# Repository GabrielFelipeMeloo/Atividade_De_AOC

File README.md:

# Atividade_De_AOC
Repositório para a entrega da atividade de ponto extra da disciplina de AOC, referente ao dia 28/10/25

### Valor: 150
150=50(mão de obra)+ 100 de custo de materiais

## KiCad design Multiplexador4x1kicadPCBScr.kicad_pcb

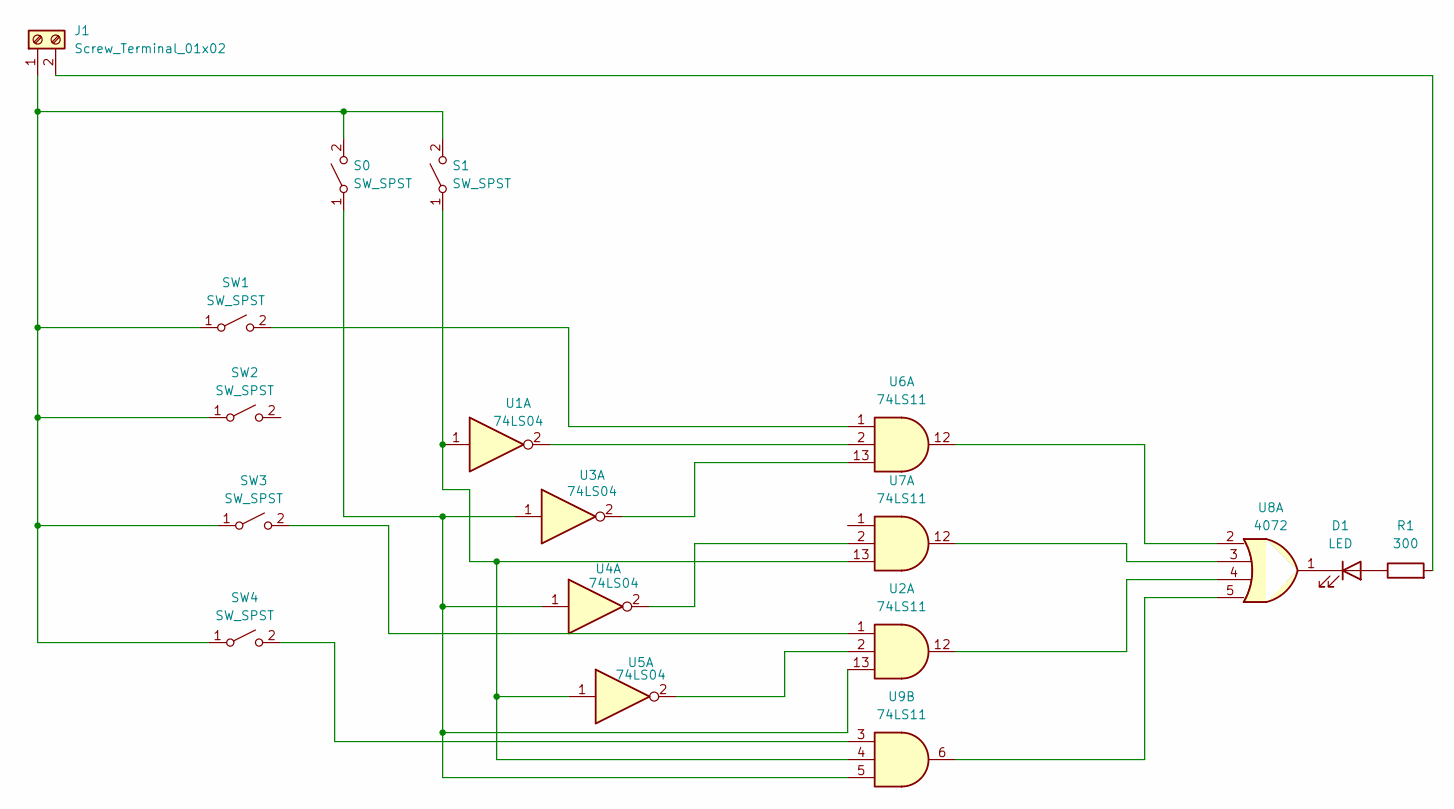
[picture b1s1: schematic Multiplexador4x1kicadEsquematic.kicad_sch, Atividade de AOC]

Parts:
D1: LED; LED_D5.0mm
J1: Screw_Terminal_01x02; PhoenixContact_MSTB_2,5_2-GF_1x02_P5.00mm_Horizontal_Thread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
R1: 300; R_Axial_DIN0207_L6.3mm_D2.5mm_P7.62mm_Horizontal
S0, S1: SW_SPST; SW_PUSH_6mm_H9.5mm
SW1, SW2, SW3, SW4: SW_SPST; SW_PUSH_6mm_H9.5mm
U1, U3, U4, U5: 74LS04; DIP-14_W7.62mm
U2, U6, U7, U9: 74LS11; DIP-14_W7.62mm
U8: 4072; DIP-14_W7.62mm

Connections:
unnamed: D1.2 (A), R1.1
unnamed: D1.1 (K), U8.1
unnamed: J1.1, S0.2 (B), S1.2 (B), SW1.1 (A), SW2.1 (A), SW3.1 (A), SW4.1 (A)
unnamed: J1.2, R1.2
unnamed: S0.1 (A), U2.13, U3.1, U4.1, U9.5
unnamed: S1.1 (A), U1.1, U5.1, U7.13, U9.4
unnamed: SW1.2 (B), U6.1
unnamed: SW3.2 (B), U2.1
unnamed: SW4.2 (B), U9.3
unnamed: U1.2, U6.2
unnamed: U2.2, U5.2
unnamed: U2.12, U8.4
unnamed: U3.2, U6.13
unnamed: U4.2, U7.2
unnamed: U6.12, U8.2
unnamed: U7.12, U8.3
unnamed: U8.5, U9.6

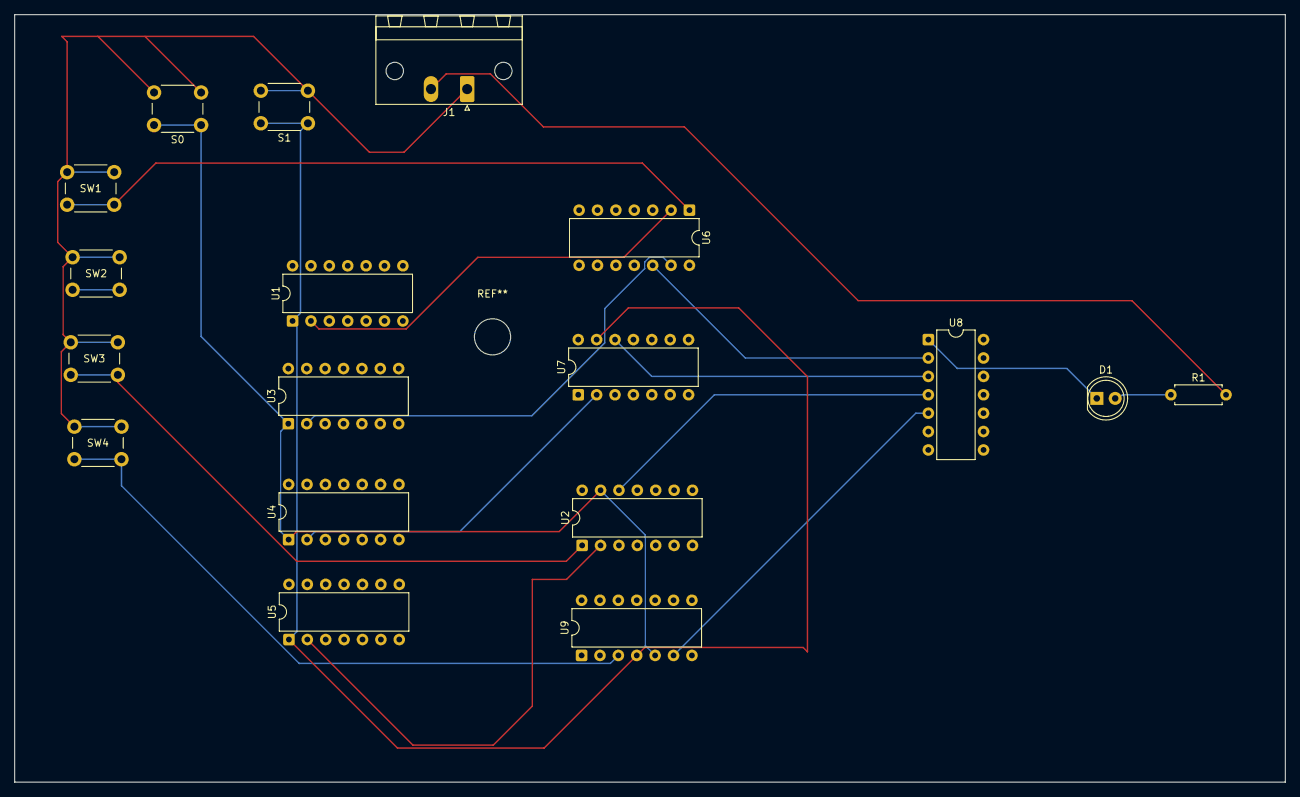
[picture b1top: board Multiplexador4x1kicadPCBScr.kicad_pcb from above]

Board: 2 copper layers, 175.5 x 106.0 mm, 18 parts (0 on the bottom side), 17 nets.
